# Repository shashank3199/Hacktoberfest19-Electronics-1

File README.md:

# Electronics-1

## Introduction
This repository contains the board design for Multiplexing 4 Line Sensing Array Modules: LSA08 (reference [here](https://www.cytron.io/p-lsa08)) to a single pair of Full Duplex Serial Lines.

## Layout

### Board File -

### Schematic File -

## Files in the Repository
The files in the repository are :

#### 4_serial_LSA.brd
This is the Board file and contains the Blueprint of the Shield Layout (Prototype).

#### 4_serial_LSA.sch
This is the Schematic file and contains the actual circuitary behind the Shield.

#### README.md
The Description file containing details about the repository. The file that you looking at right now.

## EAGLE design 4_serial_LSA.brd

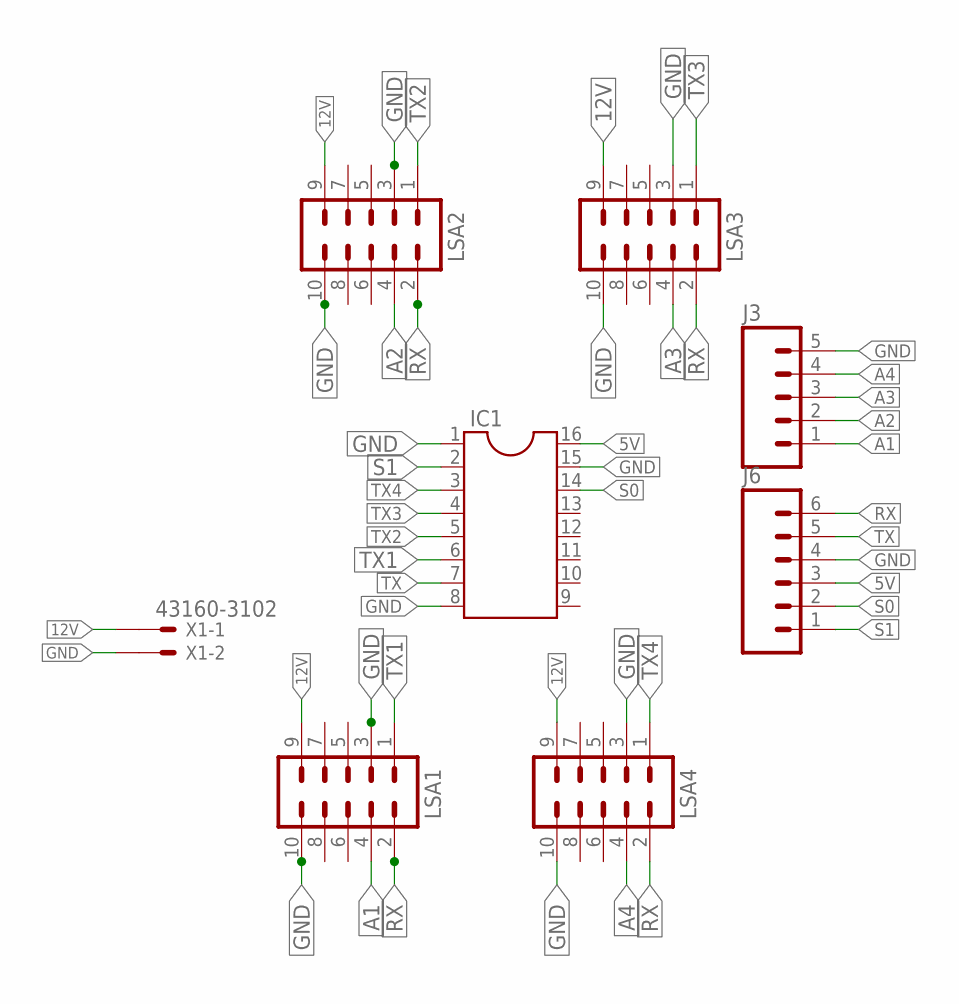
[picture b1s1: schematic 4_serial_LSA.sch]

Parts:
IC1: DIL16S; SOCKET-16
J3: M05PTH; 1X05
J6: M06SILK_FEMALE_PTH; 1X06
LSA1, LSA2, LSA3, LSA4: M05X2SHD_LOCK; 2X5-SHROUDED_LOCK
X1: 43160-3102; 43160-XX02

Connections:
5V: IC1.16, J6.3
12V: LSA1.9, LSA2.9, LSA3.9, LSA4.9, X1.1@1
A1: J3.1, LSA1.4
A2: J3.2, LSA2.4
A3: J3.3, LSA3.4
A4: J3.4, LSA4.4
GND: IC1.1, IC1.8, IC1.15, J3.5, J6.4, LSA1.3, LSA1.10, LSA2.3, LSA2.10, LSA3.3, LSA3.10, LSA4.3, LSA4.10, X1.2@1
RX: J6.6, LSA1.2, LSA2.2, LSA3.2, LSA4.2
S0: IC1.14, J6.2
S1: IC1.2, J6.1
TX: IC1.7, J6.5
TX1: IC1.6, LSA1.1
TX2: IC1.5, LSA2.1
TX3: IC1.4, LSA3.1
TX4: IC1.3, LSA4.1

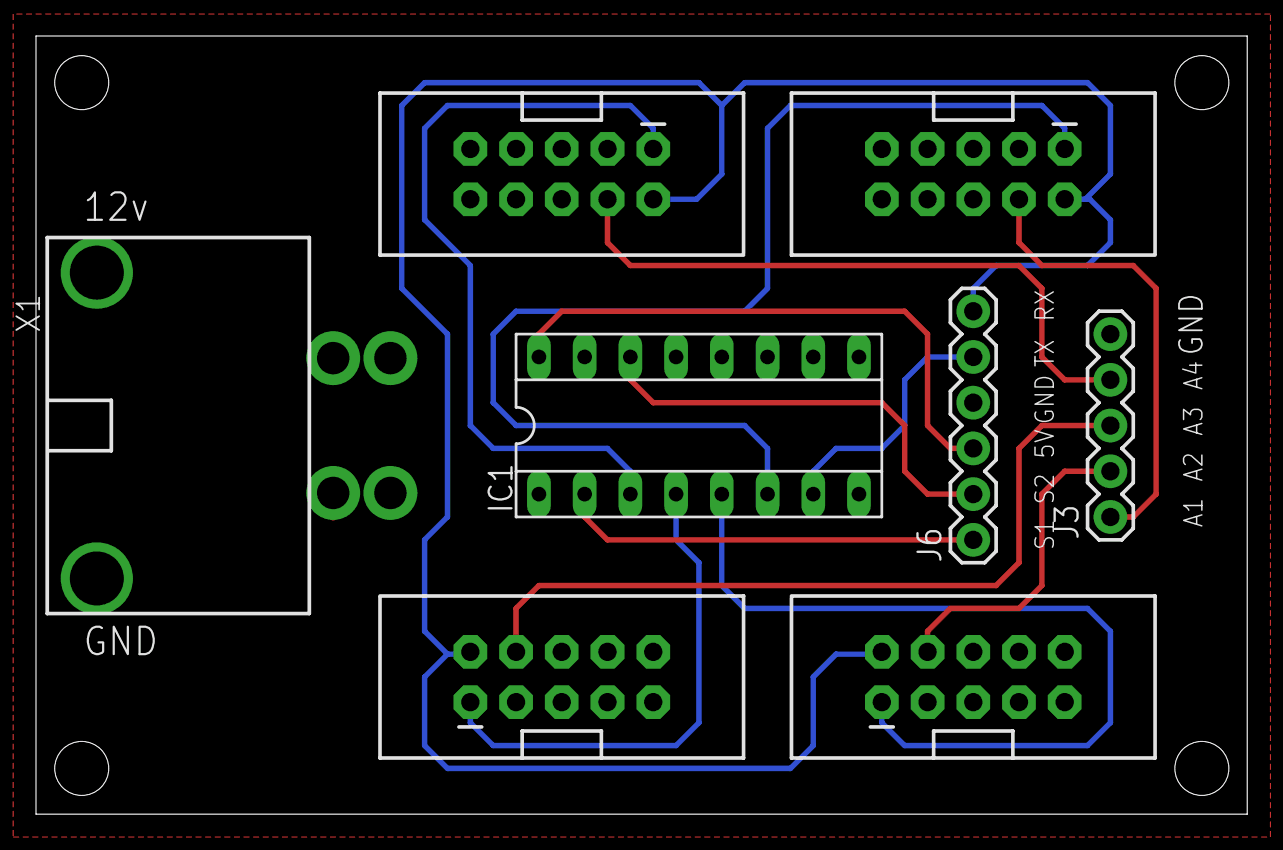
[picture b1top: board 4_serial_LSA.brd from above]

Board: 2 copper layers, 67.3 x 43.2 mm, 8 parts (0 on the bottom side), 15 nets.

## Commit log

2019-10-02 comet
2019-10-20 Added Documentation
2019-10-20 Fixed Documentation

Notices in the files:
parts and their libraries:
SparkFun-Connectors: Licensing: Creative Commons ShareAlike 4.0 International - https://creativecommons.org/licenses/by-sa/4.0
